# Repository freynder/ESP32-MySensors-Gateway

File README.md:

An ESP32 board designed to function as a Mysensors Gateway with the following features:

- Designed to fit in a cheap enclosure available from AliExpress such as [this](https://www.aliexpress.com/item/100x60x25mm-ABS-DIY-Plastic-Electronic-Project-Box-Enclosure-Instrument/32816989679.html?spm=2114.search0104.3.14.1dba6875AXjoca&ws_ab_test=searchweb0_0,searchweb201602_3_10152_10151_10065_10344_10068_10342_10325_10546_10343_10340_10548_10341_10696_10084_10083_10618_10304_10307_10820_10843_10059_100031_524_10103_10624_10623_10622_10621_10620,searchweb201603_6,ppcSwitch_5&algo_expid=a927ddcc-0543-4e6f-9c48-a30857222de3-2&algo_pvid=a927ddcc-0543-4e6f-9c48-a30857222de3&priceBeautifyAB=0)
- Footprints for RFM69 and nRF24L01 breakout boards
- uFL antenna connector for RFM69.
- Optional onboard LEDs for POWER, ERROR, TX, RX, Inclusion. Header for external LEDs if desired.
- Breakout header for I2C boards such as Si7021, HTU21D, SHTT71 and BME280 sensors.
- Breakout header for RXB6 433Mhz RF receiver
- Inclusion button and general purpose custom button. Header for external buttons if desired.
- Powered and programmed over USB. Auto-reset and flash mechanism.
- Dual regulator: RF modules have a dedicated power regulator to improve reliability.
- All parts can be sourced from AliExpress. See the BOM for links.

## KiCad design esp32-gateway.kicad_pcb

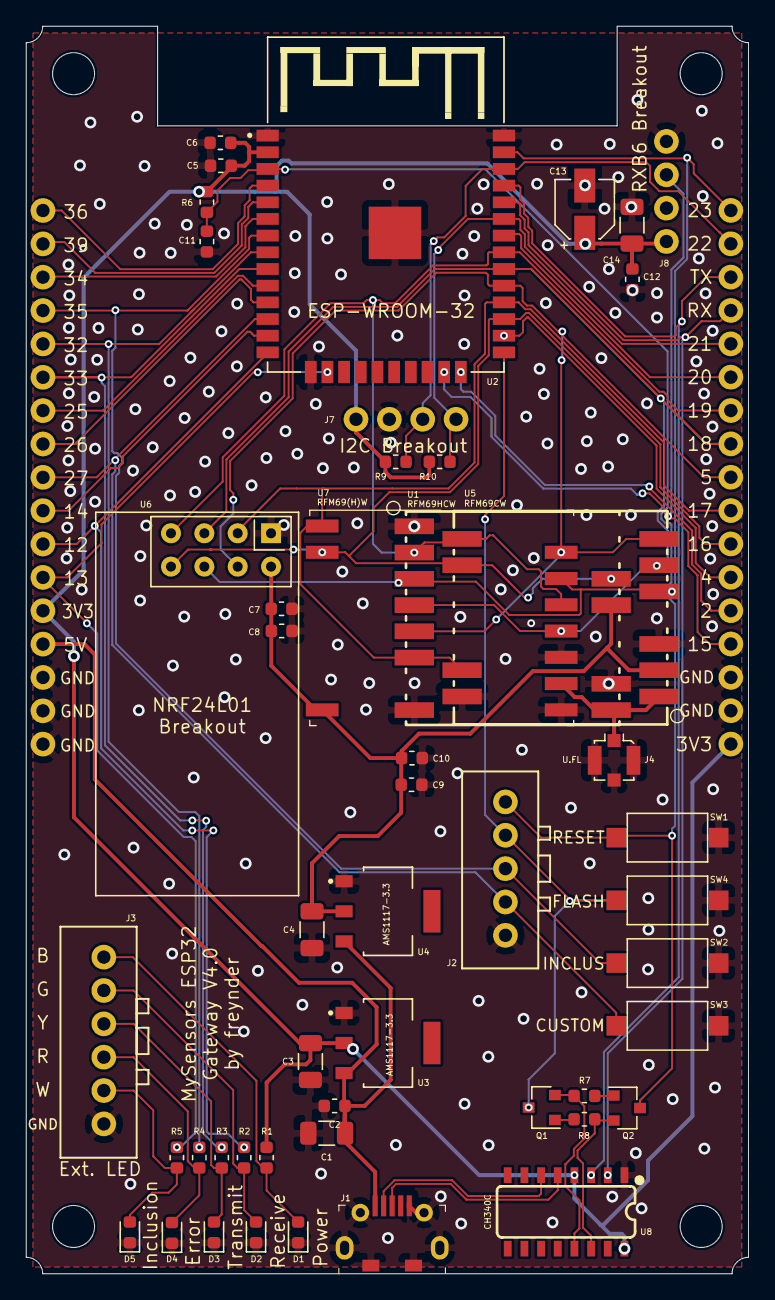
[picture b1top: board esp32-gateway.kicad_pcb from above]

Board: 2 copper layers, 55.0 x 95.0 mm, 55 parts (0 on the bottom side), 44 nets.

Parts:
C1: 4.7uF; C_1206_3216Metric
C2, C5, C9, C11, C14: 0.1uF; C_0603_1608Metric
C3, C4: 22uF; C_1206_3216Metric
C6, C10: 10uF; C_0603_1608Metric
C7: 10nF; C_0603_1608Metric
C8: 1nF; C_0603_1608Metric
C12: 10uF; C_1206_3216Metric
C13: 0.47uF; CP_Elec_4x5.4
D1: LED BLUE; LED_0603_1608Metric
D2: LED GREEN; LED_0603_1608Metric
D3: LED YELLOW; LED_0603_1608Metric
D4: LED RED; LED_0603_1608Metric
D5: LED WHITE; LED_0603_1608Metric
J1: USB_B_Micro; aliexpress_micro_USB_connector
J2: Button Connector; connector-XH2.54-01x05
J3: Ext LED header; connector-XH2.54-01x06
J4: u.FL; U.FL_Molex_MCRF_73412-0110_Vertical
J5: Header Left; 1X17_NO_SILK
J6: Header Right; 1X17_NO_SILK
J7: I2C Breakout; 1X04_NO_SILK
J8: RXB6 Breakout; 1X04_NO_SILK
MK1, MK2, MK3, MK4: Mounting_Hole; MountingHole_3.2mm_M3
Q1, Q2: Q_NPN_BEC; SOT-23
R1, R2, R5: 22; R_0603_1608Metric
R3, R4: 120; R_0603_1608Metric
R6: 10K; R_0603_1608Metric
R7, R8: 12K; R_0603_1608Metric
R9, R10: 4.7K; R_0603_1608Metric
SW1: SW_RESET; SW_SPST_CK_RS282G05A3
SW2: SW_INCLUSION; SW_SPST_CK_RS282G05A3
SW3: SW_GEN1; SW_SPST_CK_RS282G05A3
SW4: SW_BOOT; SW_SPST_CK_RS282G05A3
U1: RFM69HCW; RFM69HCW-XXXS2-MINPADS
U2: ESP-WROOM-32; MODULE_ESP-WROOM-32
U3, U4: AMS1117-3.3
U5: RFM69CW; RFM69CW-XXXS2-MINPADS
U6: NRF24L01_Breakout; nRF24L01_Breakout
U7: RFM69(H)W; HOPERF_RFM69HW-MINPADS
U8: CH340C; SO16

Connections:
+5V: C1.1, C2.1, J1.1, J5.14, U3.3, U4.3
CE-RST: J6.8, U1.6, U2.28, U5.13, U6.3, U7.1
D+: J1.3, U8.5
D-: J1.2, U8.6
DTR: Q1.2, R7.2, U8.13
EN: C11.2, J2.1, Q2.3, R6.2, SW1.1, U2.3
ESPRX: J6.14, U2.34, U8.2
ESPTX: J6.15, U2.35, U8.3
GND: C1.2, C2.2, C3.2, C4.2, C5.2, C6.2, C7.1, C8.1, C9.1, C10.1, C11.1, C12.2, C13.2, C14.2, D1.1, D2.1, D3.1, D4.1, D5.1, J1.5, J1.6, J2.5, J3.6, J4.2, J5.15, J5.16, J5.17, J6.2, J6.3, J7.2, J8.4, SW1.2, SW2.2, SW3.2, SW4.2, U1.1, U1.8, U1.10, U2.1, U2.1.1, U2.15, U2.38, U3.1, U4.1, U5.3, U5.14, U6.1, U7.9, U7.11, U8.1
IO0: J2.2, Q1.3, SW4.1, U2.25
IO2: J6.5, U2.24
IO4: J6.6, U2.26
IO5: J6.9, U1.5, U2.29, U5.7, U6.4, U7.15
IO12: J5.11, R2.2, U2.14
IO13: J5.12, R5.2, U2.16
IO14: J5.10, U2.13
IO15: J6.4, J8.3, U2.23
IO16: J6.7, U1.14, U2.27, U5.9, U6.8, U7.2
IO18: J6.10, U1.4, U2.30, U5.6, U6.5, U7.12
IO19: J6.11, U1.2, U2.31, U5.8, U6.7, U7.13
IO20: J6.12, U2.32
IO21: J6.13, J7.4, R10.1, U2.33
IO22: J6.16, J7.3, R9.1, U2.36
IO23: J6.17, U1.3, U2.37, U5.5, U6.6, U7.14
IO25: J5.7, U2.10
IO26: J5.8, U2.11
IO27: J2.4, J5.9, SW3.1, U2.12
IO32: J5.5, R4.2, U2.8
IO33: J5.6, R3.2, U2.9
IO34: J5.3, U2.6
IO35: J2.3, J5.4, SW2.1, U2.7
LEDB: C3.1, C5.1, C6.1, C12.1, C13.1, C14.1, J5.13, J6.1, J7.1, J8.1, R1.2, R6.1, R9.2, R10.2, U2.2, U3.2, U8.4, U8.16
unnamed: D1.2, J3.1, R1.1
unnamed: D2.2, J3.2, R2.1
unnamed: D3.2, J3.3, R3.1
unnamed: D4.2, J3.4, R4.1
unnamed: D5.2, J3.5, R5.1
unnamed: Q1.1, R8.2
unnamed: Q2.1, R7.1
RFMANT: J4.1, U1.9, U5.1, U7.10
RFPOW: C4.1, C7.2, C8.2, C9.2, C10.2, U1.13, U4.2, U5.2, U6.2, U7.8
RTS: Q2.2, R8.1, U8.14
SENSOR_VN: J5.2, U2.5
SENSOR_VP: J5.1, U2.4

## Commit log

2018-07-07 Initial
2018-07-07 Added schema
2018-07-07 Added readme, optimized traces, added decoupling capacitors
2018-07-07 Some small trace optimizations
2018-08-10 Added test results and some images
2018-08-11 Updated test results
2018-08-13 Fixed initial issues and made font larger.
    Issues fixed are:
    - TX and RX LEDs connected to IO34 and IO35 do not work as ESP32 does not support pull-up on those pins.
    - Wrong labeling of RX led (mentioned 36 but should be 34)
    - C4 capacitor was located near the CH340G chip but should have been near AMS1117
    - Missing pull-up on EN pin.
    - Missing capacitor to ground on EN pin.
2018-08-13 Fixed initial issues and made font larger.
    Issues fixed are:
    - TX and RX LEDs connected to IO34 and IO35 do not work as ESP32 does not support pull-up on those pins.
    - Wrong labeling of RX led (mentioned 36 but should be 34)
    - C4 capacitor was located near the CH340G chip but should have been near AMS1117
    - Missing pull-up on EN pin.
    - Missing capacitor to ground on EN pin.
2018-08-13 Add missing reference to silk screen (cosmetic)
2018-08-19 Added dimensions
2018-08-29 Corrected error and made nicer traces
    - inclusion button was connected to IO33, however IO33 was already in
    use for transmission led. Connected inclusion button to IO35 instead.
    - aligned traces better and maximized ground plane for a nicer board.
2018-09-04 Fixed design error for 3.3v power
2018-09-06 Apply net design rules
2018-09-15 Major redesign.
    - Changed headers to XH2.54 connectors for leds and buttons
    - Added secondary regulator to power RF modules
    - Changed RFM69 footprints to remove unused pads
    - Changed CHG340G chip to CHG340C, eliminating the crystal
    - Relayed all traces for cleaner design
    - Added capacitors at USB input power
2018-09-15 git cleanup
2018-09-15 Silkscreen optimization plus BOM
2018-09-15 Fixed power routing error
2018-09-16 Added I2C breakout header
2018-09-16 Added Breakout for RXB6 433Mhz RF receiver
2018-09-19 Added pullup pins for I2C
    Please note that some breakout boards come with pullups included. It is
    advisable to desolder those or not include the pullup pins on the board.
